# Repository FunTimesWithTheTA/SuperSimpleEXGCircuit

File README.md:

# SuperSimpleEXGCircuit
Super simple circuit for measuring potential signals such as ECG, EEG, EOG, etc.

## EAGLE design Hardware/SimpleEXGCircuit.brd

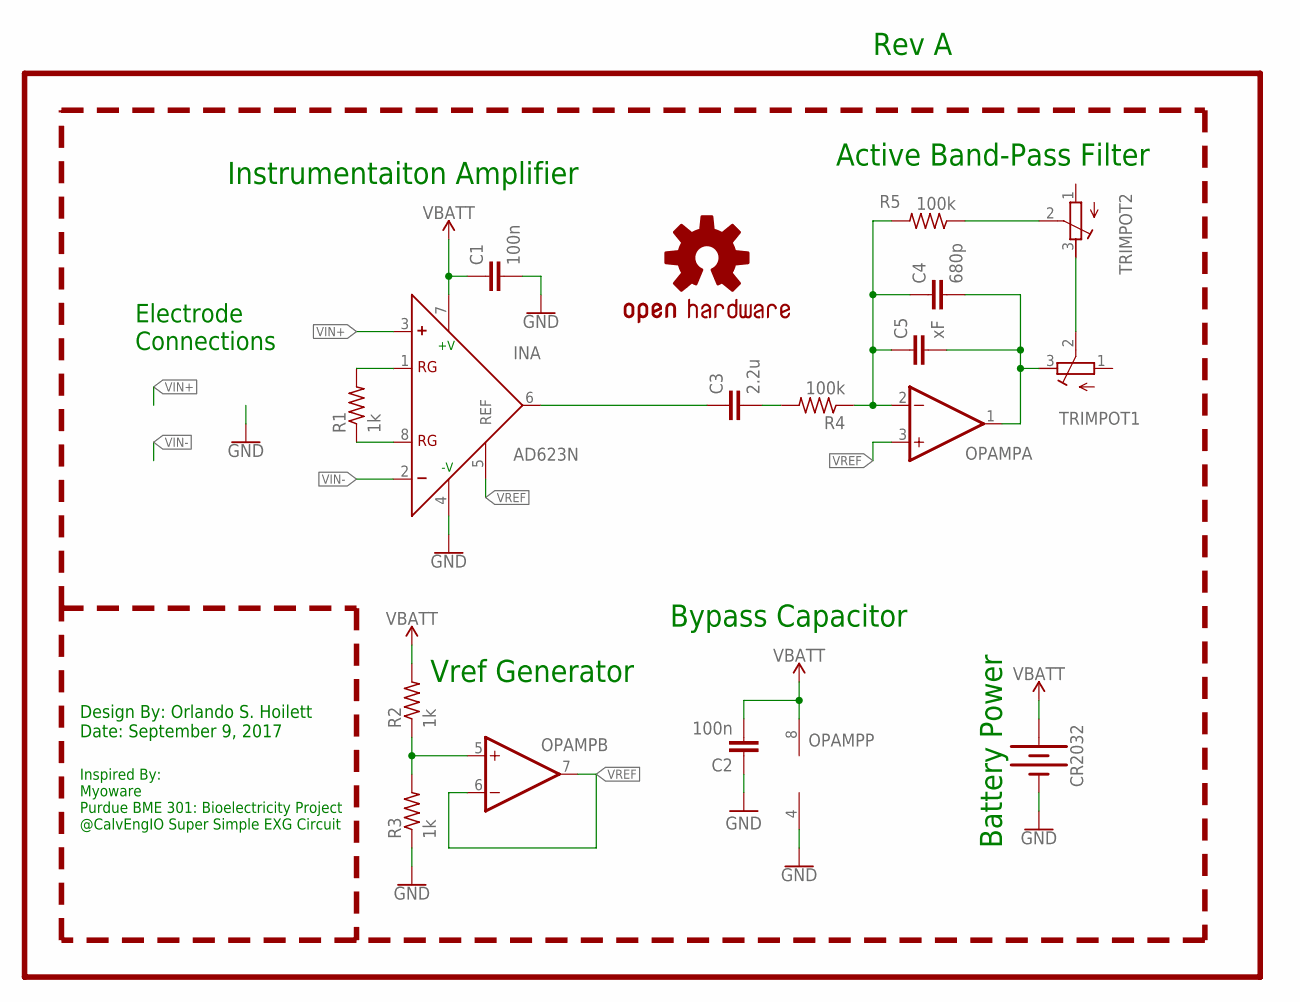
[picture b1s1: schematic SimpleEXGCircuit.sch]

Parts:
C1, C2: 100n; C050-030X075
C3: 2.2u; C050-030X075
C4: 680p; C050-030X075
C5: xF; C050-030X075
CR2032: BATTERY-20MM_SMD_4LEGS_OVERPASTE; BATTCON_20MM_4LEGS_OVERPASTE
INA: AD623N; DIL08
LOGO1: OSHW-LOGOS; OSHW-LOGO-S
OPAMP: OP-DUALDIP08; DIL08
R1, R2, R3: 1k; 0207/10
R4, R5: 100k; 0207/10
TRIMPOT1, TRIMPOT2: TRIM-POT-P160; 16MMROTARYPOT

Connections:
GND: C1.2, C2.1, CR2032.2 (-), INA.4 (-V), OPAMP.4 (V-), R3.1
unnamed: R5.1, TRIMPOT2.2 (S)
unnamed: TRIMPOT1.2 (S), TRIMPOT2.3 (E)
unnamed: OPAMP.5 (+IN), R2.1, R3.2
unnamed: C3.2, R4.2
unnamed: C4.1, C5.1, OPAMP.2 (-IN), R4.1, R5.2
unnamed: C3.1, INA.6 (OUT)
unnamed: INA.1 (RG), R1.2
unnamed: INA.8 (RG), R1.1
OUT: C4.2, C5.2, OPAMP.1 (OUT), TRIMPOT1.3 (E)
VIN+: INA.3 (+)
VIN-: INA.2 (-)
VREF: INA.5 (REF), OPAMP.3 (+IN), OPAMP.6 (-IN), OPAMP.7 (OUT)
V_BATT: C1.1, C2.2, CR2032.1 (+), INA.7 (+V), OPAMP.8 (V+), R2.2

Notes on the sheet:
Instrumentaiton Amplifier
Active Band-Pass Filter
Vref Generator
Battery Power
Bypass Capacitor
Rev A
Electrode Connections
Design By: Orlando S. Hoilett Date: September 9, 2017
Inspired By: Myoware Purdue BME 301: Bioelectricity Project @CalvEngIO Super Simple EXG Circuit

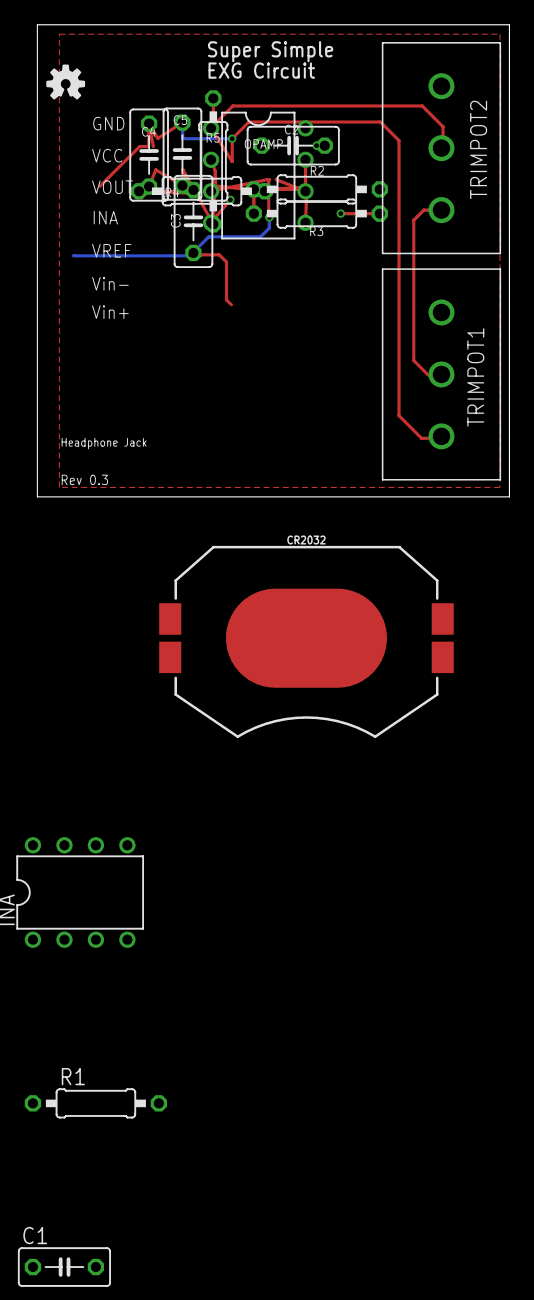
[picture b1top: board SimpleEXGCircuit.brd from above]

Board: 2 copper layers, 38.1 x 38.1 mm, 16 parts (0 on the bottom side), 12 nets.

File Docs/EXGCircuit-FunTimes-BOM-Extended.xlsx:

@CalvEngIO LiPo Battery Breadboard Supply with Charging Rev E |  |  |  |  |  |  |  |  |  |  | Total | #REF! |  | Price Break | #REF! | 9.4376750000000005 | 9.3469750000000005 | 9.0436050000000012 | #REF! |  | Cost w/ Price Break | 18.854749999999999 | #VALUE! | 36.171875000000007 | 15.490365000000001 | 15.471228750000003 |  | Bulk Cost | 451.64375000000007 | 1659.7854999999997 | #VALUE! | 7811.9825000000001 | 14715.228749999998
BOM # | Comment | Designator | Description | Mounting Type | Package | Manufacturer | Manufacturer Part Number | Supplier | Supplier Part Number | Price per unit | Quantity | Price Total |  |  | 25 | 100 | 250 | 500 | 1000 |  |  | 25 | 100 | 250 | 500 | 1000 |  |  | 25 | 100 | 250 | 500 | 1000
1 | AD623 | INA | IC OPAMP INSTR 800KHZ RRO 8DIP | THT | 8DIP | Analog Devices | AD623ANZ | Digi-Key | AD623ANZ-ND | 6.31 | 1 | 6.31 |  |  | 5.3550000000000004 | 4.641 | 4.641 | 3.9508000000000001 | 3.3319999999999999 |  |  | 5.3550000000000004 | 4.641 | 4.641 | 3.9508000000000001 | 3.3319999999999999 |  |  | 133.875 | 464.1 | 1160.25 | 1975.4 | 3332
2 | MCP6002 |  | General Purpose Amplifier 2 Circuit Rail-to-Rail 8-MSOP | THT | 8DIP | Microchip Technology | MCP6002-I/P | Digi-Key | MCP6002-I/P-ND | 0.35 | 1 | 0.35 |  |  | 0.29399999999999998 | 0.26250000000000001 | 0.26250000000000001 | 0.26250000000000001 | 0.26250000000000001 |  |  | 0.25 | #VALUE! | 6.25 |  | 0.25 | #VALUE! | 250 |  | 0.25 | #VALUE! | 25
3 | 1k resistor | R1,R2,R3,R6 |  | THT |  |  |  | Digi-Key |  |  | 1 | 0 |  |  | 0.317 | 0.1973 | 0.1973 | 0.13496 | 0.10382 |  |  | 0.317 | 0.1973 | 0.1973 | 0.13496 | 0.10382 |  |  | 7.9249999999999998 | 19.73 | 49.325000000000003 | 67.48 | 103.82
4 | 100k resistor | R4,R5 |  | THT |  |  |  | Digi-Key |  |  | 1 | 0 |  |  | 0.37440000000000001 | 0.30559999999999998 | 0.27444000000000002 | 0.26196000000000003 | 0.26196000000000003 |  |  | 0.37440000000000001 | 0.30559999999999998 | 0.27444000000000002 | 0.26196000000000003 | 0.26196000000000003 |  |  | 9.36 | 30.56 | 68.61 | 130.98000000000002 | 261.96000000000004
5 | 100nF capacitor | C1,C2 |  | THT
6 | 2.2uF capacitor | C3 |  | THT |  |  |  | Digi-Key |  |  | 2 | 0 |  |  | 0.2424 | 0.18340000000000001 | 0.1298 | 0.10382 | 7.9600000000000004E-2 |  |  | 0.48480000000000001 | 0.36680000000000001 | 0.2596 | 0.20763999999999999 | 0.15920000000000001 |  |  | 12.120000000000001 | 36.68 | 64.900000000000006 | 103.82 | 159.20000000000002
7 | 680pF capacitor | C4 |  | THT |  |  |  | Digi-Key |  |  | 1 | 0 |  |  | 0.24675000000000002 | 0.20317499999999999 | 0.20317499999999999 | 0.160605 | 0.13786874999999998 |  |  | 0.24675000000000002 | 0.20317499999999999 | 0.20317499999999999 | 0.160605 | 0.13786874999999998 |  |  | 6.1687500000000011 | 20.317499999999999 | 50.793749999999996 | 80.302499999999995 | 137.86874999999998
8 | Potentiometer |  | 1M Ohm 1 Gang Linear Panel Mount Potentiometer None 1 Turn Conductive Plastic 0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 | THT | Panel Mount | TT Electronics/BI | P160KN-0EC15B1MEG | Digi-Key | 987-1711-ND | 0.76 |  | #REF! |  | 0.61599999999999999 | #REF! | 0 |  | 0.56100000000000005 | #REF! | 280.5 |  | 0.53900000000000003 | #REF! | 13.475000000000001 |  | 0.50600000000000001 | #REF! | 506 |  | 0.41799999999999998 | #REF! | 41.8
9 | LED | PWR |  | THT |  |  |  | Digi-Key |  |  | 1 | 0 |  |  | 5.4800000000000001E-2 | 3.85E-2 | 3.2559999999999999E-2 | 3.0099999999999998E-2 | 2.6599999999999999E-2 |  |  | 5.4800000000000001E-2 | 3.85E-2 | 3.2559999999999999E-2 | 3.0099999999999998E-2 | 2.6599999999999999E-2 |  |  | 1.37 | 3.85 | 8.1399999999999988 | 15.049999999999999 | 26.599999999999998
10 | CR2032 | CR2032 | 20MM COIN BATT BREAKOUT W/SWITCH |  |  | Adafruit Industries LLC | 1871 | Digi-Key | 1528-1458-ND | 3.3 | 3 | 9.8999999999999986 |  |  | 3.5 | 3.5 | 3.5 | 3.5 | 3.5 |  |  | 10.5 | 10.5 | 10.5 | 10.5 | 10.5 |  |  | 262.5 | 1050 | 2625 | 5250 | 10500
11 | ECG Electrodes | VIN+,VIN-,GND |  | NA |  |  |  | Digi-Key |  |  | 5 | 0 |  |  | 9.4E-2 | 4.3999999999999997E-2 | 4.3999999999999997E-2 | 3.0859999999999999E-2 | 2.555E-2 |  |  | 0.47 | 0.21999999999999997 | 0.21999999999999997 | 0.15429999999999999 | 0.12775 |  |  | 11.75 | 21.999999999999996 | 54.999999999999993 | 77.149999999999991 | 127.75
11 |  |  |  | SMD |  |  |  | Digi-Key |  |  | 2 | 0 |  |  | 9.7000000000000003E-2 | 4.5600000000000002E-2 | 4.5600000000000002E-2 | 3.2000000000000001E-2 | 2.6499999999999999E-2 |  |  | 0.19400000000000001 | 9.1200000000000003E-2 | 9.1200000000000003E-2 | 6.4000000000000001E-2 | 5.2999999999999999E-2 |  |  | 4.8500000000000005 | 9.120000000000001 | 22.8 | 32 | 53
12 |  |  |  | SMD |  |  |  | Digi-Key |  |  | 1 | 0 |  |  | 1.2999999999999999E-2 | 5.5999999999999999E-3 | 5.5999999999999999E-3 | 4.0000000000000001E-3 | 3.15E-3 |  |  | 1.2999999999999999E-2 | 5.5999999999999999E-3 | 5.5999999999999999E-3 | 4.0000000000000001E-3 | 3.15E-3 |  |  | 0.32500000000000001 | 0.55999999999999994 | 1.4 | 2 | 3.15
13 |  |  |  | SMD |  |  |  | Digi-Key |  |  | 3 | 0 |  |  | 1.4E-2 | 5.4999999999999997E-3 | 5.4999999999999997E-3 | 5.4999999999999997E-3 | 2.47E-3 |  |  | 4.2000000000000003E-2 | 1.6500000000000001E-2 | 1.6500000000000001E-2 | 1.6500000000000001E-2 | 7.4099999999999999E-3 |  |  | 1.05 | 1.6500000000000001 | 4.125 | 8.25 | 7.41
 | Arduino |  |  | SMD |  |  |  | Digi-Key |  |  | 1 | 0 |  |  | 1.4E-2 | 5.4999999999999997E-3 | 5.4999999999999997E-3 | 5.4999999999999997E-3 | 2.47E-3 |  |  | 1.4E-2 | 5.4999999999999997E-3 | 5.4999999999999997E-3 | 5.4999999999999997E-3 | 2.47E-3 |  |  | 0.35000000000000003 | 0.54999999999999993 | 1.375 | 2.75 | 2.4699999999999998
 | USB Cable
 | ECG Electrodes

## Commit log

2018-06-21 updates from the previous semester
2018-06-21 updates from Fall 2017 semester

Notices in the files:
Hardware/SimpleEXGCircuit.brd:
Creative Commons License
CC BY-SA-4.0
parts and their libraries:
SparkFun-Aesthetics: Licensing: Creative Commons ShareAlike 4.0 International - https://creativecommons.org/licenses/by-sa/4.0
